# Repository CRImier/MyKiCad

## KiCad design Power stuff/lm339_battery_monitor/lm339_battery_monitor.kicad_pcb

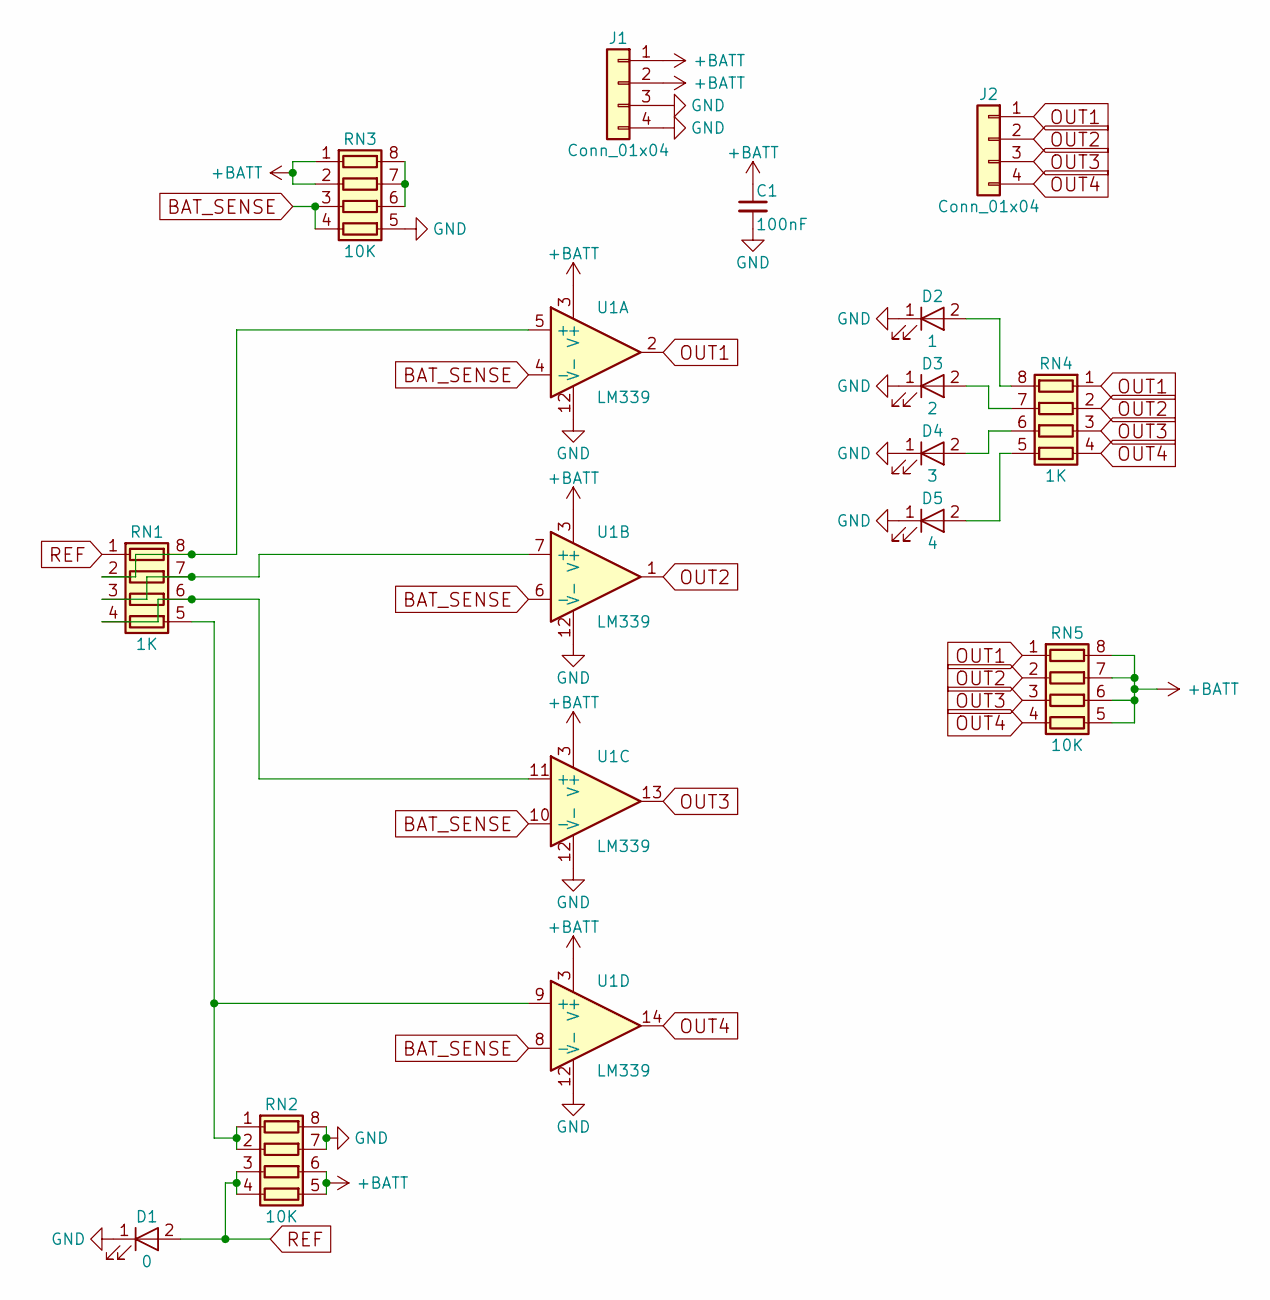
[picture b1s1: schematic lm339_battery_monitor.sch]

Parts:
C1: 100nF; C_0805
D1: 0; LED_0805
D2: 1; LED_0805
D3: 2; LED_0805
D4: 3; LED_0805
D5: 4; LED_0805
J1, J2: Conn_01x04; Pin_Header_Straight_1x04_Pitch2.54mm
RN1, RN4: 1K; R_Array_Convex_4x0402
RN2, RN3, RN5: 10K; R_Array_Convex_4x0402
U1: LM339; SOIC-14_3.9x8.7mm_Pitch1.27mm

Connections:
+BATT: C1.1, J1.1, J1.2, RN2.5 (R4.2), RN2.6 (R3.2), RN3.1 (R1.1), RN3.2 (R2.1), RN5.5 (R4.2), RN5.6 (R3.2), RN5.7 (R2.2), RN5.8 (R1.2), U1.3 (V+)
BAT_SENSE: RN3.3 (R3.1), RN3.4 (R4.1), U1.4 (-), U1.6 (-), U1.8 (-), U1.10 (-)
GND: C1.2, D1.1 (K), D2.1 (K), D3.1 (K), D4.1 (K), D5.1 (K), J1.3, J1.4, RN2.7 (R2.2), RN2.8 (R1.2), RN3.5 (R4.2), U1.12 (V-)
unnamed: D2.2 (A), RN4.8 (R1.2)
unnamed: D3.2 (A), RN4.7 (R2.2)
unnamed: D4.2 (A), RN4.6 (R3.2)
unnamed: D5.2 (A), RN4.5 (R4.2)
unnamed: RN1.2 (R2.1), RN1.8 (R1.2), U1.5 (+)
unnamed: RN1.3 (R3.1), RN1.7 (R2.2), U1.7 (+)
unnamed: RN1.4 (R4.1), RN1.6 (R3.2), U1.11 (+)
unnamed: RN1.5 (R4.2), RN2.1 (R1.1), RN2.2 (R2.1), U1.9 (+)
unnamed: RN3.6 (R3.2), RN3.7 (R2.2), RN3.8 (R1.2)
OUT1: J2.1, RN4.1 (R1.1), RN5.1 (R1.1), U1.2
OUT2: J2.2, RN4.2 (R2.1), RN5.2 (R2.1), U1.1
OUT3: J2.3, RN4.3 (R3.1), RN5.3 (R3.1), U1.13
OUT4: J2.4, RN4.4 (R4.1), RN5.4 (R4.1), U1.14
REF: D1.2 (A), RN1.1 (R1.1), RN2.3 (R3.1), RN2.4 (R4.1)

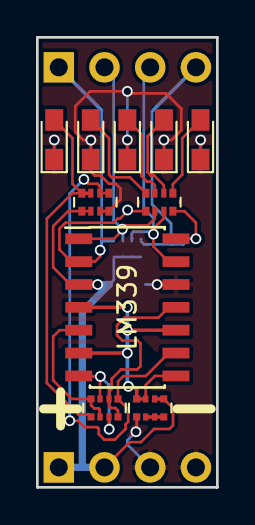
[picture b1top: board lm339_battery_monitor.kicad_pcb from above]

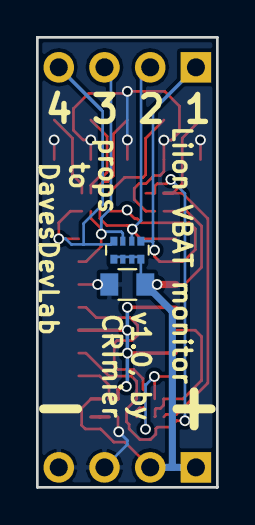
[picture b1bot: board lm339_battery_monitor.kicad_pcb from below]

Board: 2 copper layers, 10.0 x 25.0 mm, 14 parts (2 on the bottom side), 17 nets.

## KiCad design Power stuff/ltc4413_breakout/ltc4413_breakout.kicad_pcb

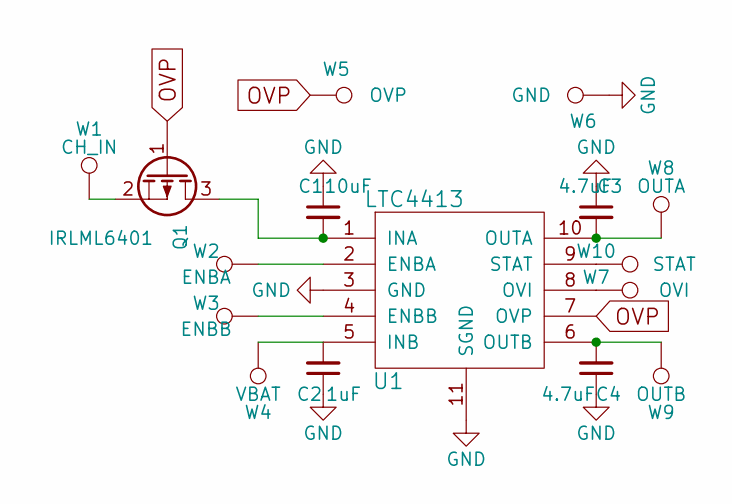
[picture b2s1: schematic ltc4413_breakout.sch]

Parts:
C1: 10uF; C_0805_HandSoldering
C2: 1uF; C_0805_HandSoldering
C3, C4: 4.7uF; C_0805_HandSoldering
Q1: IRLML6401; SOT-23_Handsoldering
U1: LTC4413; DFN-10-1EP_3x3mm_Pitch0.5mm
W1: CH_IN; Measurement_Point_Round-SMD-Pad_Big
W2: ENBA; Measurement_Point_Round-SMD-Pad_Small
W3: ENBB; Measurement_Point_Round-SMD-Pad_Small
W4: VBAT; Measurement_Point_Round-SMD-Pad_Big
W5: OVP; Measurement_Point_Round-SMD-Pad_Small
W6: GND; Measurement_Point_Round-SMD-Pad_Small
W7: OVI; Measurement_Point_Round-SMD-Pad_Small
W8: OUTA; Measurement_Point_Round-SMD-Pad_Big
W9: OUTB; Measurement_Point_Round-SMD-Pad_Big
W10: STAT; Measurement_Point_Round-SMD-Pad_Small

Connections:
GND: C1.1, C2.1, C3.1, C4.1, U1.3 (GND), U1.11 (SGND), W6.1
unnamed: C1.2, Q1.3 (D), U1.1 (INA)
unnamed: C2.2, U1.5 (INB), W4.1
unnamed: C3.2, U1.10 (OUTA), W8.1
unnamed: C4.2, U1.6 (OUTB), W9.1
unnamed: Q1.2 (S), W1.1
unnamed: U1.2 (ENBA), W2.1
unnamed: U1.4 (ENBB), W3.1
unnamed: U1.8 (OVI), W7.1
unnamed: U1.9 (STAT), W10.1
OVP: Q1.1 (G), U1.7 (OVP), W5.1

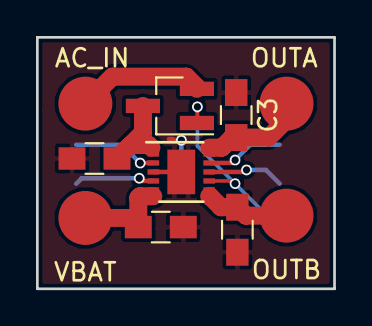
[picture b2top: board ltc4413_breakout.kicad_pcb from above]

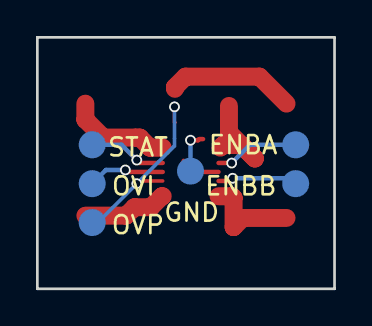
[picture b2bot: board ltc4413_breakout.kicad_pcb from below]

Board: 2 copper layers, 16.5 x 14.0 mm, 16 parts (6 on the bottom side), 11 nets.

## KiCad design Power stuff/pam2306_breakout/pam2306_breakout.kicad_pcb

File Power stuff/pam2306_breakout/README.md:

# PAM2306 breakout

A breakout for PAM2306 dual buck switching regulator,
exposing both of the regulator units. It works with the adjustable version of this chip.
The board is laid out according to the regulator datasheet layout standards,
and is made to be as small as possible.

## Notes

- Pin headers are arranged in a way that this board can be plugged into a breadboard.
- Signal names are silkscreened on the board, top and bottom layers.
- This board is untested and there's no guarantees of fitness.

## Info

- Software: Kicad 7
- Version: 1
- PCB size: 18x13.5mm
- Layer count: 2

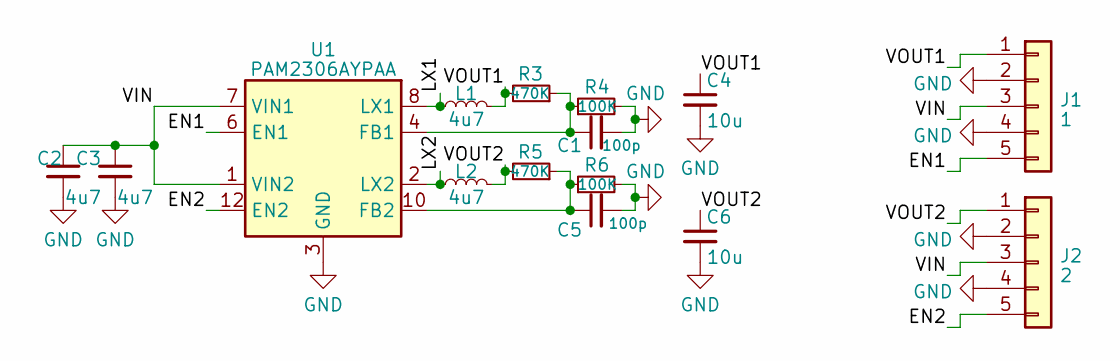
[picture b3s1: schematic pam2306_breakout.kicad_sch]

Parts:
C1, C5: 100p; C_0603_1608Metric
C2, C3: 4u7; C_0805_2012Metric
C4, C6: 10u; C_0805_2012Metric
J1: 1; PinHeader_1x05_P2.54mm_Vertical
J2: 2; PinHeader_1x05_P2.54mm_Vertical
L1, L2: 4u7; L_Murata_23S4R7C
R3, R5: 470K; R_0603_1608Metric
R4, R6: 100K; R_0603_1608Metric
U1: PAM2306AYPAA; WDFN-12-1EP_3x3mm_P0.45mm_EP1.7x2.5mm

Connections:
/EN1: J1.5, U1.6 (EN1)
/EN2: J2.5, U1.12 (EN2)
/LX1: L1.1, U1.8 (LX1)
/LX2: L2.1, U1.2 (LX2)
/VIN: C2.1, C3.1, J1.3, J2.3, U1.1 (VIN2), U1.7 (VIN1)
/VOUT1: C4.1, J1.1, L1.2, R3.2
/VOUT2: C6.1, J2.1, L2.2, R5.2
GND: C1.2, C2.2, C3.2, C4.2, C5.2, C6.2, J1.2, J1.4, J2.2, J2.4, R4.2, R6.2, U1.3 (GND), U1.9 (GND), U1.13 (GND)
unnamed: C1.1, R3.1, R4.1, U1.4 (FB1)
unnamed: C5.1, R5.1, R6.1, U1.10 (FB2)

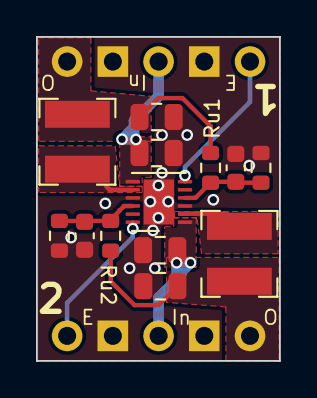
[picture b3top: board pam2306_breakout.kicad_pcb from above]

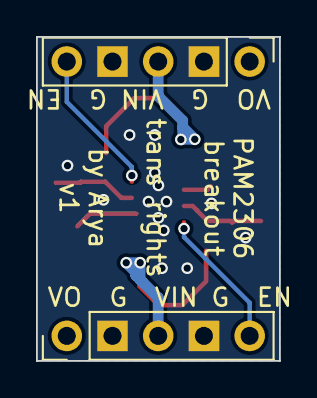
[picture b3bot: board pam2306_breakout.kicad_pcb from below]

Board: 2 copper layers, 13.5 x 18.0 mm, 15 parts (2 on the bottom side), 10 nets.

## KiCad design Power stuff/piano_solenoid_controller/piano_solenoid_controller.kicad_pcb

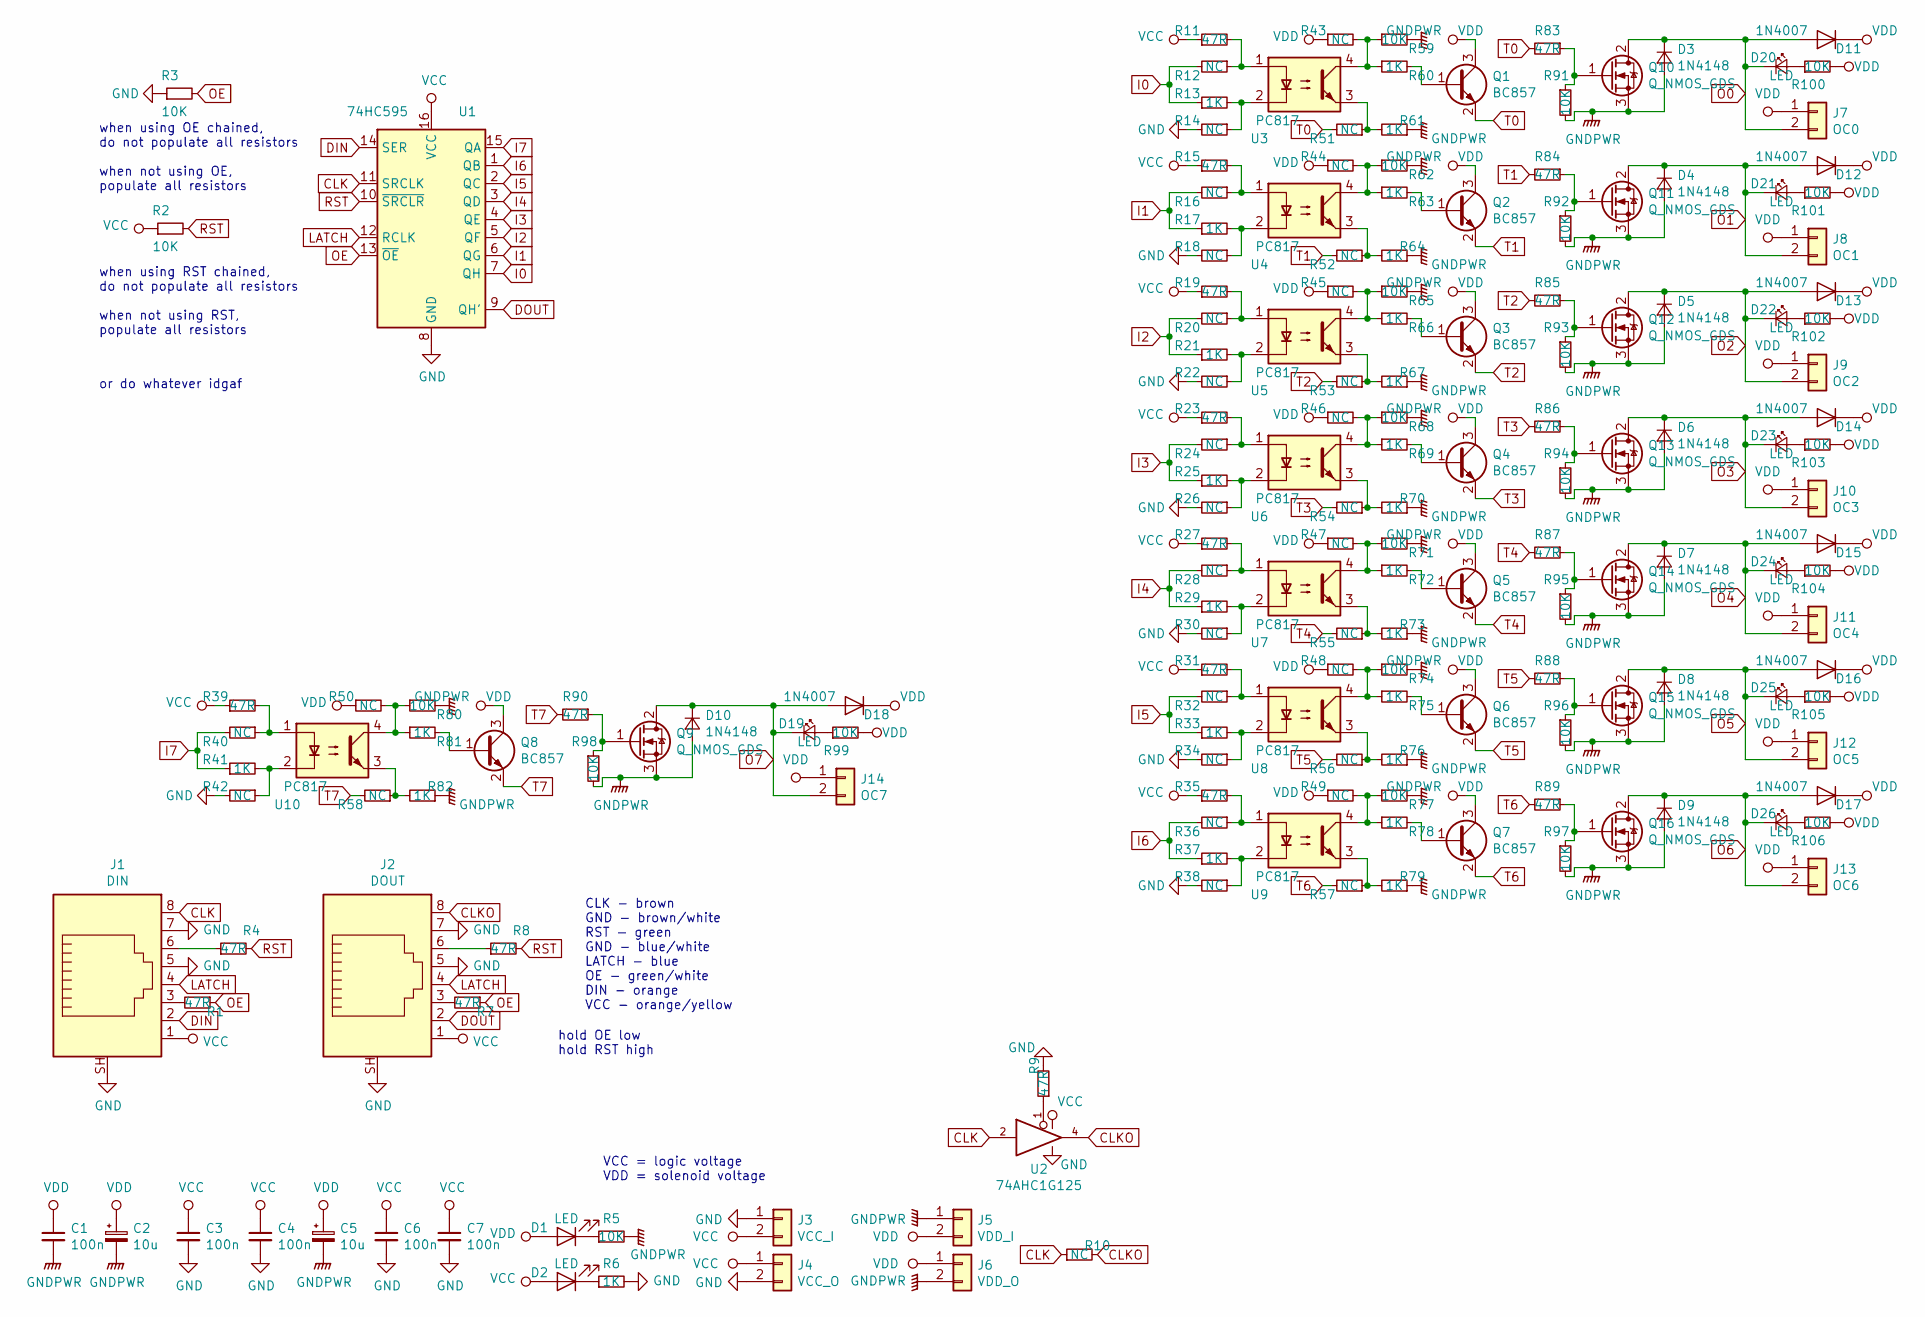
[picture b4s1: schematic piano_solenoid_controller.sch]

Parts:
C1, C3, C4, C6, C7: 100n; C_0805_2012Metric_Pad1.15x1.40mm_HandSolder
C2, C5: 10u; CP_Radial_D10.0mm_P2.50mm_P5.00mm
D1, D2, D19, D20, D21, D22, D23, D24, D25, D26: LED; LED_0805_2012Metric_Pad1.15x1.40mm_HandSolder
D3: 1N4148; D_DO-35_SOD27_P7.62mm_Horizontal
D4, D5, D6, D7, D8, D9, D10: 1N4148; D_DO-34_SOD68_P7.62mm_Horizontal
D11, D12, D13, D14, D15, D16, D17, D18: 1N4007; D_SMC-RM10_Universal_Handsoldering
J1: DIN; RJ45_Amphenol_RJHSE5380
J2: DOUT; RJ45_Amphenol_RJHSE5380
J3: VCC_I; PinHeader_1x02_P2.54mm_Vertical
J4: VCC_O; PinHeader_1x02_P2.54mm_Vertical
J5: VDD_I; PhoenixContact_MC_1,5_2-G-3.81_1x02_P3.81mm_Horizontal
J6: VDD_O; PhoenixContact_MC_1,5_2-G-3.81_1x02_P3.81mm_Horizontal
J7: OC0; PhoenixContact_MC_1,5_2-G-3.81_1x02_P3.81mm_Horizontal
J8: OC1; PhoenixContact_MC_1,5_2-G-3.81_1x02_P3.81mm_Horizontal
J9: OC2; PhoenixContact_MC_1,5_2-G-3.81_1x02_P3.81mm_Horizontal
J10: OC3; PhoenixContact_MC_1,5_2-G-3.81_1x02_P3.81mm_Horizontal
J11: OC4; PhoenixContact_MC_1,5_2-G-3.81_1x02_P3.81mm_Horizontal
J12: OC5; PhoenixContact_MC_1,5_2-G-3.81_1x02_P3.81mm_Horizontal
J13: OC6; PhoenixContact_MC_1,5_2-G-3.81_1x02_P3.81mm_Horizontal
J14: OC7; PhoenixContact_MC_1,5_2-G-3.81_1x02_P3.81mm_Horizontal
Q1, Q2, Q3, Q4, Q5, Q6, Q7, Q8: BC857; SOT-23_Handsoldering
Q9, Q10, Q11, Q12, Q13, Q14, Q15, Q16: Q_NMOS_GDS; TO-220-3_Vertical
R1, R4, R7, R8, R9, R11, R15, R19, R23, R27, R31, R35, R39, R83, R84, R85, R86, R87, R88, R89, R90: 47R; R_0805_2012Metric_Pad1.15x1.40mm_HandSolder
R2, R3, R5, R59, R62, R65, R68, R71, R74, R77, R80, R91, R92, R93, R94, R95, R96, R97, R98, R99, R100, R101, R102, R103, R104, R105, R106: 10K; R_0805_2012Metric_Pad1.15x1.40mm_HandSolder
R6, R13, R17, R21, R25, R29, R33, R37, R41, R60, R61, R63, R64, R66, R67, R69, R70, R72, R73, R75, R76, R78, R79, R81, R82: 1K; R_0805_2012Metric_Pad1.15x1.40mm_HandSolder
R10, R12, R14, R16, R18, R20, R22, R24, R26, R28, R30, R32, R34, R36, R38, R40, R42, R43, R44, R45, R46, R47, R48, R49, R50, R51, R52, R53, R54, R55, R56, R57, R58: NC; R_0805_2012Metric_Pad1.15x1.40mm_HandSolder
U1: 74HC595; SOIC-16_4.55x10.3mm_P1.27mm
U2: 74AHC1G125; SOT-353_SC-70-5_Handsoldering
U3, U4, U5, U6, U7, U8, U9, U10: PC817; DIP-4_W7.62mm

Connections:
CLK: J1.8, R10.1, U1.11 (SRCLK), U2.2
CLKO: J2.8, R10.2, U2.4
DIN: J1.2, U1.14 (SER)
DOUT: J2.2, U1.9 (QH')
GND: C3.2, C4.2, C6.2, C7.2, J1.5, J1.7, J1.SH, J2.5, J2.7, J2.SH, J3.1, J4.2, R3.1, R6.2, R9.2, R14.2, R18.2, R22.2, R26.2, R30.2, R34.2, R38.2, R42.2, U1.8 (GND), U2.3 (GND)
GNDPWR: C1.2, C2.2, C5.2, D3.2 (A), D4.2 (A), D5.2 (A), D6.2 (A), D7.2 (A), D8.2 (A), D9.2 (A), D10.2 (A), J5.1, J6.2, Q9.3 (S), Q10.3 (S), Q11.3 (S), Q12.3 (S), Q13.3 (S), Q14.3 (S), Q15.3 (S), Q16.3 (S), R5.2, R59.2, R61.1, R62.2, R64.1, R65.2, R67.1, R68.2, R70.1, R71.2, R73.1, R74.2, R76.1, R77.2, R79.1, R80.2, R82.1, R91.2, R92.2, R93.2, R94.2, R95.2, R96.2, R97.2, R98.2
I0: R12.2, R13.1, U1.7 (QH)
I1: R16.2, R17.1, U1.6 (QG)
I2: R20.2, R21.1, U1.5 (QF)
I3: R24.2, R25.1, U1.4 (QE)
I4: R28.2, R29.1, U1.3 (QD)
I5: R32.2, R33.1, U1.2 (QC)
I6: R36.2, R37.1, U1.1 (QB)
I7: R40.2, R41.1, U1.15 (QA)
LATCH: J1.4, J2.4, U1.12 (RCLK)
unnamed: D1.1 (K), R5.1
unnamed: D2.1 (K), R6.1
unnamed: D19.2 (A), R99.1
unnamed: D20.2 (A), R100.1
unnamed: D21.2 (A), R101.1
unnamed: D22.2 (A), R102.1
unnamed: D23.2 (A), R103.1
unnamed: D24.2 (A), R104.1
unnamed: D25.2 (A), R105.1
unnamed: D26.2 (A), R106.1
unnamed: J1.3, R1.2
unnamed: J1.6, R4.1
unnamed: J2.3, R7.2
unnamed: J2.6, R8.1
unnamed: Q1.1 (B), R60.2
unnamed: Q2.1 (B), R63.2
unnamed: Q3.1 (B), R66.2
unnamed: Q4.1 (B), R69.2
unnamed: Q5.1 (B), R72.2
unnamed: Q6.1 (B), R75.2
unnamed: Q7.1 (B), R78.2
unnamed: Q8.1 (B), R81.2
unnamed: Q9.1 (G), R90.1, R98.1
unnamed: Q10.1 (G), R83.1, R91.1
unnamed: Q11.1 (G), R84.1, R92.1
unnamed: Q12.1 (G), R85.1, R93.1
unnamed: Q13.1 (G), R86.1, R94.1
unnamed: Q14.1 (G), R87.1, R95.1
unnamed: Q15.1 (G), R88.1, R96.1
unnamed: Q16.1 (G), R89.1, R97.1
unnamed: R9.1, U2.1
unnamed: R11.2, R12.1, U3.1
unnamed: R13.2, R14.1, U3.2
unnamed: R15.2, R16.1, U4.1
unnamed: R17.2, R18.1, U4.2
unnamed: R19.2, R20.1, U5.1
unnamed: R21.2, R22.1, U5.2
unnamed: R23.2, R24.1, U6.1
unnamed: R25.2, R26.1, U6.2
unnamed: R27.2, R28.1, U7.1
unnamed: R29.2, R30.1, U7.2
unnamed: R31.2, R32.1, U8.1
unnamed: R33.2, R34.1, U8.2
unnamed: R35.2, R36.1, U9.1
unnamed: R37.2, R38.1, U9.2
unnamed: R39.2, R40.1, U10.1
unnamed: R41.2, R42.1, U10.2
unnamed: R43.2, R59.1, R60.1, U3.4
unnamed: R44.2, R62.1, R63.1, U4.4
unnamed: R45.2, R65.1, R66.1, U5.4
unnamed: R46.2, R68.1, R69.1, U6.4
unnamed: R47.2, R71.1, R72.1, U7.4
unnamed: R48.2, R74.1, R75.1, U8.4
unnamed: R49.2, R77.1, R78.1, U9.4
unnamed: R50.2, R80.1, R81.1, U10.4
unnamed: R51.1, R61.2, U3.3
unnamed: R52.1, R64.2, U4.3
unnamed: R53.1, R67.2, U5.3
unnamed: R54.1, R70.2, U6.3
unnamed: R55.1, R73.2, U7.3
unnamed: R56.1, R76.2, U8.3
unnamed: R57.1, R79.2, U9.3
unnamed: R58.1, R82.2, U10.3
O0: D3.1 (K), D11.2 (A), D20.1 (K), J7.2, Q10.2 (D)
O1: D4.1 (K), D12.2 (A), D21.1 (K), J8.2, Q11.2 (D)
O2: D5.1 (K), D13.2 (A), D22.1 (K), J9.2, Q12.2 (D)
O3: D6.1 (K), D14.2 (A), D23.1 (K), J10.2, Q13.2 (D)
O4: D7.1 (K), D15.2 (A), D24.1 (K), J11.2, Q14.2 (D)
O5: D8.1 (K), D16.2 (A), D25.1 (K), J12.2, Q15.2 (D)
O6: D9.1 (K), D17.2 (A), D26.1 (K), J13.2, Q16.2 (D)
O7: D10.1 (K), D18.2 (A), D19.1 (K), J14.2, Q9.2 (D)
OE: R1.1, R3.2, R7.1, U1.13 (~OE)
RST: R2.2, R4.2, R8.2, U1.10 (~SRCLR)
T0: Q1.2 (E), R51.2, R83.2
T1: Q2.2 (E), R52.2, R84.2
T2: Q3.2 (E), R53.2, R85.2
T3: Q4.2 (E), R54.2, R86.2
T4: Q5.2 (E), R55.2, R87.2
T5: Q6.2 (E), R56.2, R88.2
T6: Q7.2 (E), R57.2, R89.2
T7: Q8.2 (E), R58.2, R90.2
VCC: C3.1, C4.1, C6.1, C7.1, D2.2 (A), J1.1, J2.1, J3.2, J4.1, R2.1, R11.1, R15.1, R19.1, R23.1, R27.1, R31.1, R35.1, R39.1, U1.16 (VCC), U2.5 (VCC)
VDD: C1.1, C2.1, C5.1, D1.2 (A), D11.1 (K), D12.1 (K), D13.1 (K), D14.1 (K), D15.1 (K), D16.1 (K), D17.1 (K), D18.1 (K), J5.2, J6.1, J7.1, J8.1, J9.1, J10.1, J11.1, J12.1, J13.1, J14.1, Q1.3 (C), Q2.3 (C), Q3.3 (C), Q4.3 (C), Q5.3 (C), Q6.3 (C), Q7.3 (C), Q8.3 (C), R43.1, R44.1, R45.1, R46.1, R47.1, R48.1, R49.1, R50.1, R99.2, R100.2, R101.2, R102.2, R103.2, R104.2, R105.2, R106.2

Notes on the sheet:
VCC = logic voltage VDD = solenoid voltage
when using OE chained, do not populate all resistors when not using OE, populate all resistors
when using RST chained, do not populate all resistors when not using RST, populate all resistors
CLK - brown GND - brown/white RST - green GND - blue/white LATCH - blue OE - green/white DIN - orange VCC - orange/yellow
hold OE low hold RST high
or do whatever idgaf

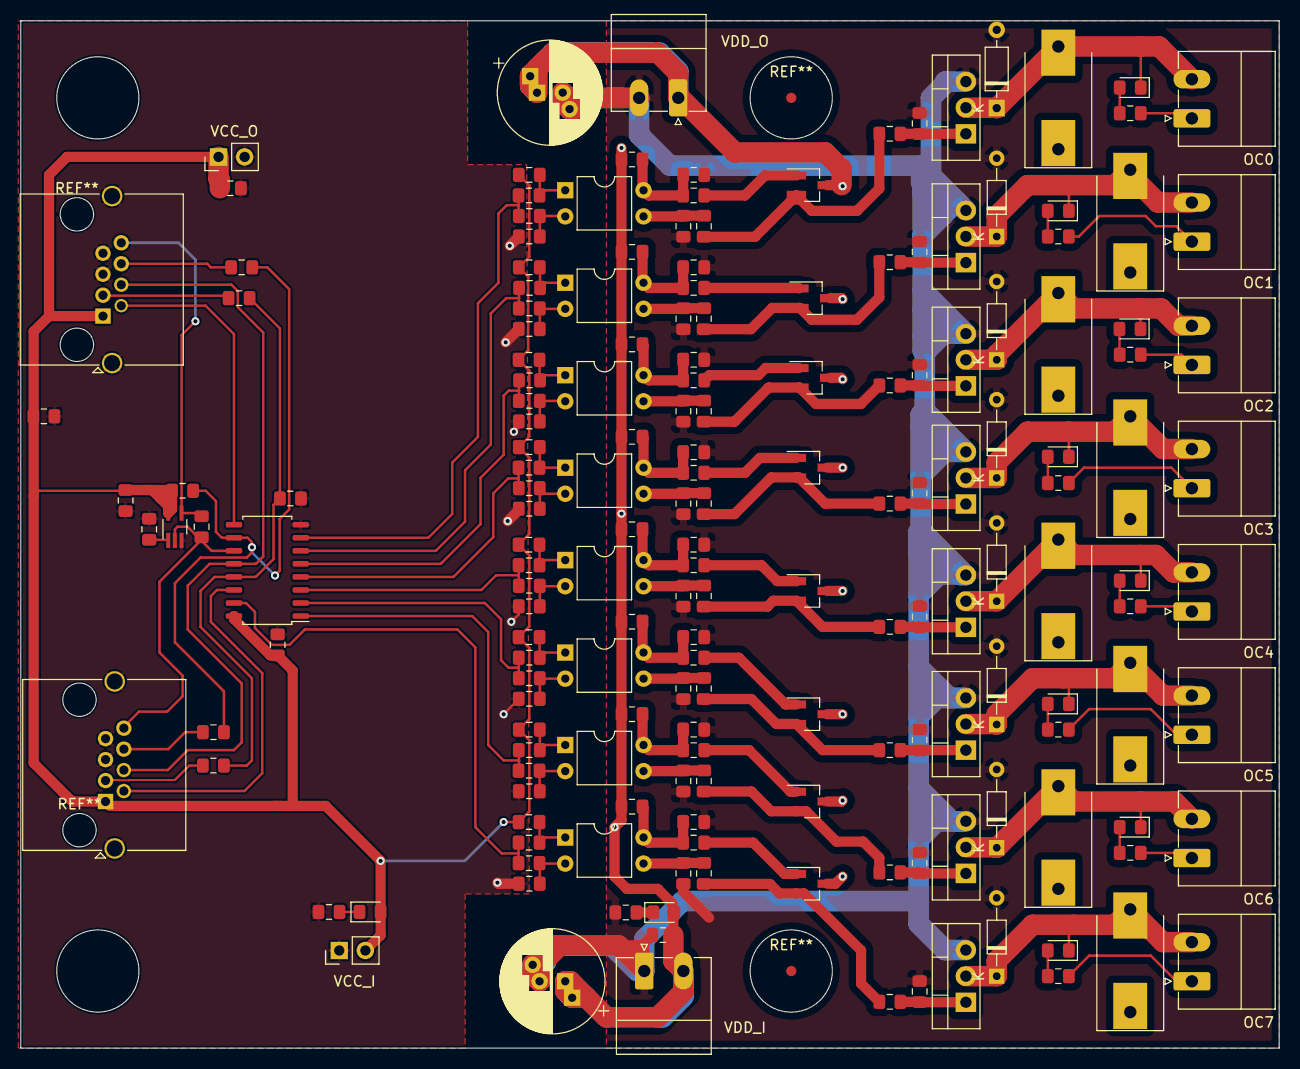
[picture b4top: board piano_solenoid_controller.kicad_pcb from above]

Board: 2 copper layers, 122.5 x 100.0 mm, 179 parts (0 on the bottom side), 98 nets.

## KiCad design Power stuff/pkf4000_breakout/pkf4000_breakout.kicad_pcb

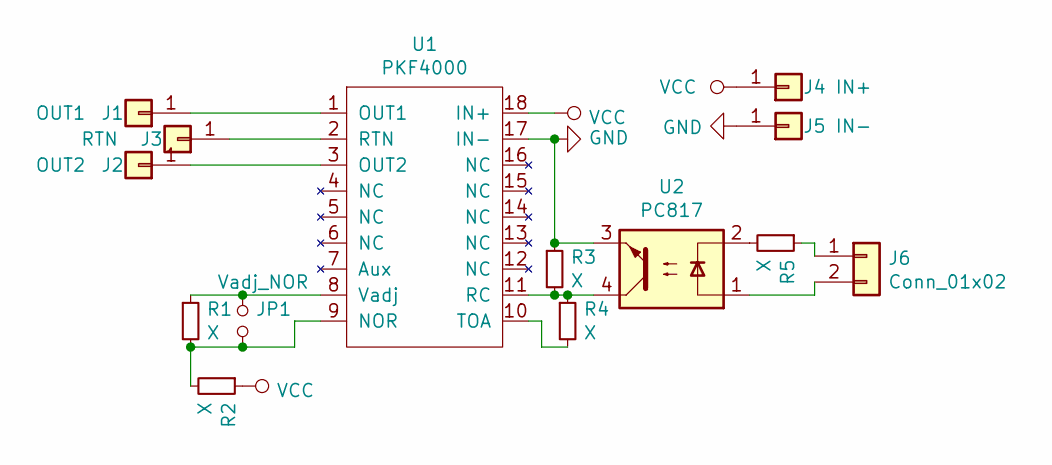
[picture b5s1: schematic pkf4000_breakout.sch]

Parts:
J1: OUT1; WireConnection_2.00mmDrill
J2: OUT2; WireConnection_2.00mmDrill
J3: RTN; WireConnection_2.00mmDrill
J4: IN+; WireConnection_2.00mmDrill
J5: IN-; WireConnection_2.00mmDrill
J6: Conn_01x02; PinHeader_1x02_P2.54mm_Vertical
JP1: Vadj_NOR; SolderJumper-2_P1.3mm_Open_Pad1.0x1.5mm
R1, R2, R3, R4, R5: X; R_0805_2012Metric_Pad1.15x1.40mm_HandSolder
U1: PKF4000; PKF4000_THT_SMD
U2: PC817; DIP-4_W7.62mm

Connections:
GND: J5.1, R3.1, U1.17 (IN-), U2.3
unnamed: J1.1, U1.1 (OUT1)
unnamed: J2.1, U1.3 (OUT2)
unnamed: J3.1, U1.2 (RTN)
unnamed: J6.1, R5.1
unnamed: J6.2, U2.1
unnamed: JP1.1, R1.2, R2.2, U1.9 (NOR)
unnamed: JP1.2, R1.1, U1.8 (Vadj)
unnamed: R3.2, R4.1, U1.11 (RC), U2.4
unnamed: R4.2, U1.10 (TOA)
unnamed: R5.2, U2.2
VCC: J4.1, R2.1, U1.18 (IN+)

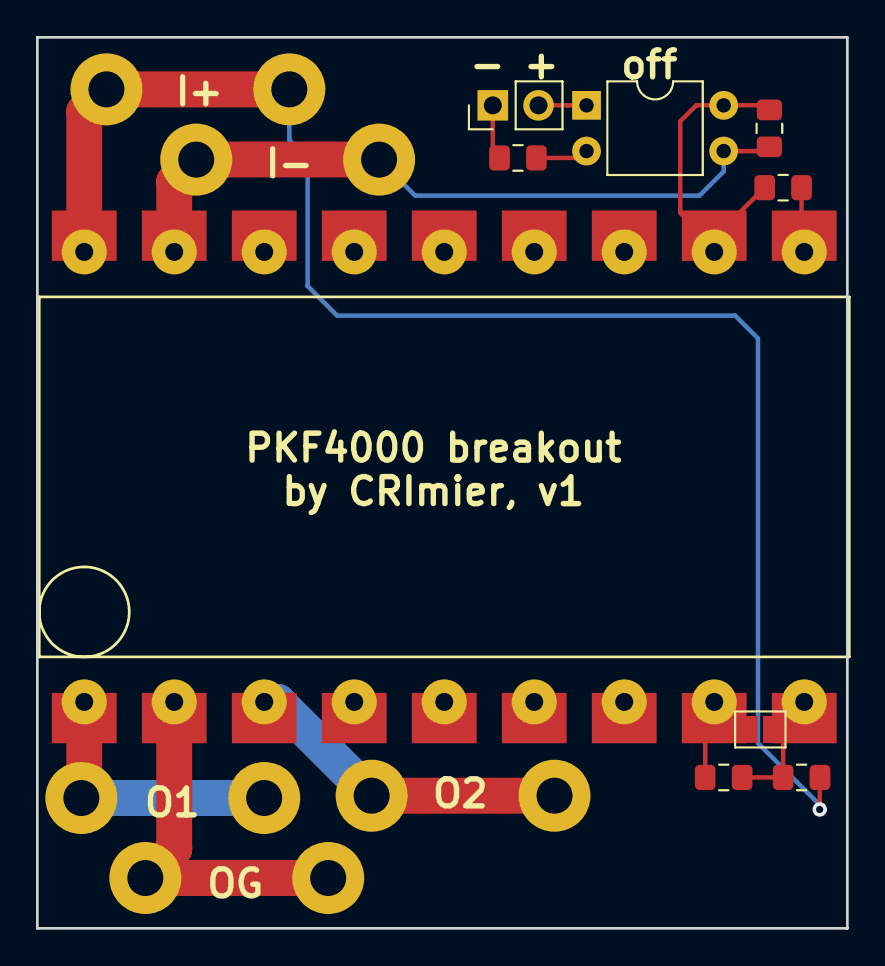
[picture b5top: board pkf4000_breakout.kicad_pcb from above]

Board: 2 copper layers, 45.0 x 49.5 mm, 14 parts (0 on the bottom side), 12 nets.

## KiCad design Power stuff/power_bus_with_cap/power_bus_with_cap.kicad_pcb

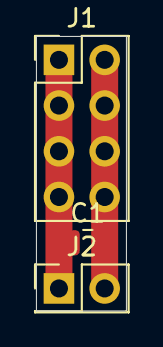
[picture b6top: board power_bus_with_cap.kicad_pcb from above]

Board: 2 copper layers, 5.0 x 15.2 mm, 3 parts (0 on the bottom side), 2 nets.

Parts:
C1: C_Small; C_0805_2012Metric
J1: Conn_02x04_Odd_Even; PinHeader_2x04_P2.54mm_Vertical
J2: Conn_01x02; PinHeader_2x01_P2.54mm_Vertical

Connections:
unnamed: C1.1, J1.1, J1.3, J1.5, J1.7, J2.1
unnamed: C1.2, J1.2, J1.4, J1.6, J1.8, J2.2

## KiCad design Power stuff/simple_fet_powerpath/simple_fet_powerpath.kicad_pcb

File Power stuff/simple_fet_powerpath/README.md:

# Simple FET power path

This is a simple power path that uses a FET, Schottky diode and a pulldown resistor.
Descriptions on how it works are easy to find online. This is a PCB version that's easy to bodge
onto some project of yours that could use such a powerpath.

This powerpath is intended for situations like where you have to power an input of 3.3V LDO
from either 5V USB or LiIon battery voltage, depending on what's present. It could also be used with i.e.
10V input and a 2s LiIon battery, but you'll have to do the math on suitability and FET parameters yourself.

If your load brownouts when you switch the power source (especially from USB to battery),
decrease the value of the pulldown resistor.

Signal names are silkscreened on the board's top and bottom layers.

- PCB size: 15*11mm
- Layer count: 2

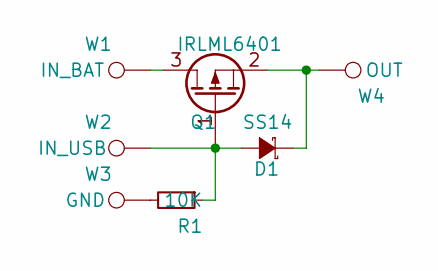
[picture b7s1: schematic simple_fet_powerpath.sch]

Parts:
D1: SS14; D_MiniMELF_Handsoldering
Q1: IRLML6401; SOT-23_Handsoldering
R1: 10K; R_0805_HandSoldering
W1: IN_BAT; Measurement_Point_Round-TH_Big
W2: IN_USB; Measurement_Point_Round-TH_Big
W3: GND; Measurement_Point_Round-TH_Big
W4: OUT; Measurement_Point_Round-TH_Big

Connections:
unnamed: D1.1 (K), Q1.2 (S), W4.1
unnamed: D1.2 (A), Q1.1 (G), R1.1, W2.1
unnamed: Q1.3 (D), W1.1
unnamed: R1.2, W3.1

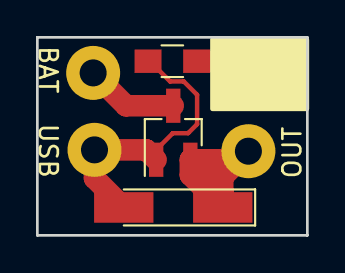
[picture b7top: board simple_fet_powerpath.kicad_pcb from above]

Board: 2 copper layers, 15.0 x 11.0 mm, 7 parts (0 on the bottom side), 4 nets.

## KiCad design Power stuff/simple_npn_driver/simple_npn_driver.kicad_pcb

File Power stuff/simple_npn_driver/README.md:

# Simple NPN driver

A simple small driver board with an NPN transistor that can be used to drive a small relay, motor or other device.
Has a base resistor and a pulldown resistor from IN, a diode to limit backwards EMF, as well as a capacitor between GND and VCC.
Also has a small 0R 0603 resistor in series with VCC that acts as a pseudo-fuse.

- PCB size: 13mmx7.75mm
- Layer count: 2

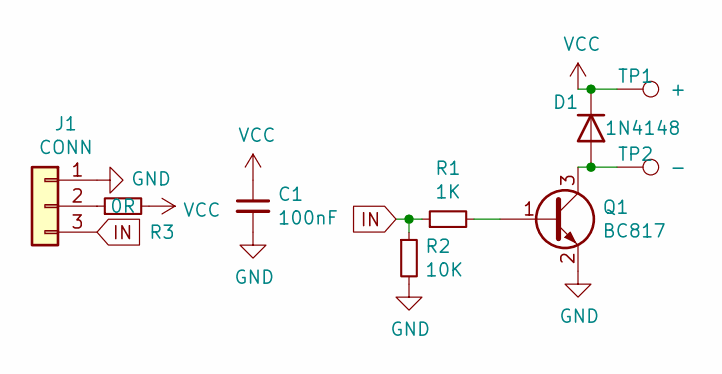
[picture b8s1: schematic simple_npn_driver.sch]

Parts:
C1: 100nF; C_0805_2012Metric
D1: 1N4148; D_SOD-123
J1: CONN; PinHeader_1x03_P2.54mm_Vertical
Q1: BC817; SOT-23
R1: 1K; R_0805_2012Metric
R2: 10K; R_0805_2012Metric
R3: 0R; R_0603_1608Metric
TP1: +; TestPoint_Pad_D2.0mm
TP2: -; TestPoint_Pad_D2.0mm

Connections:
GND: C1.2, J1.1, Q1.2 (E), R2.2
IN: J1.3, R1.1, R2.1
unnamed: D1.2 (A), Q1.3 (C), TP2.1
unnamed: J1.2, R3.1
unnamed: Q1.1 (B), R1.2
VCC: C1.1, D1.1 (K), R3.2, TP1.1

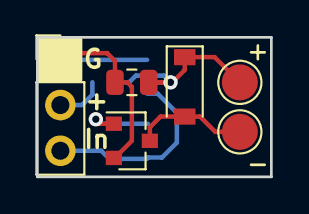
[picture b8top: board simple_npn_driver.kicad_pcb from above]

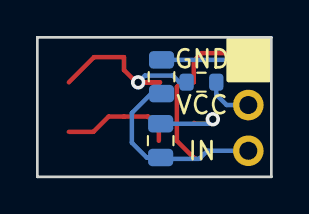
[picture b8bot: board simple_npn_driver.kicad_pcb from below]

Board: 2 copper layers, 13.0 x 7.8 mm, 9 parts (3 on the bottom side), 6 nets.
